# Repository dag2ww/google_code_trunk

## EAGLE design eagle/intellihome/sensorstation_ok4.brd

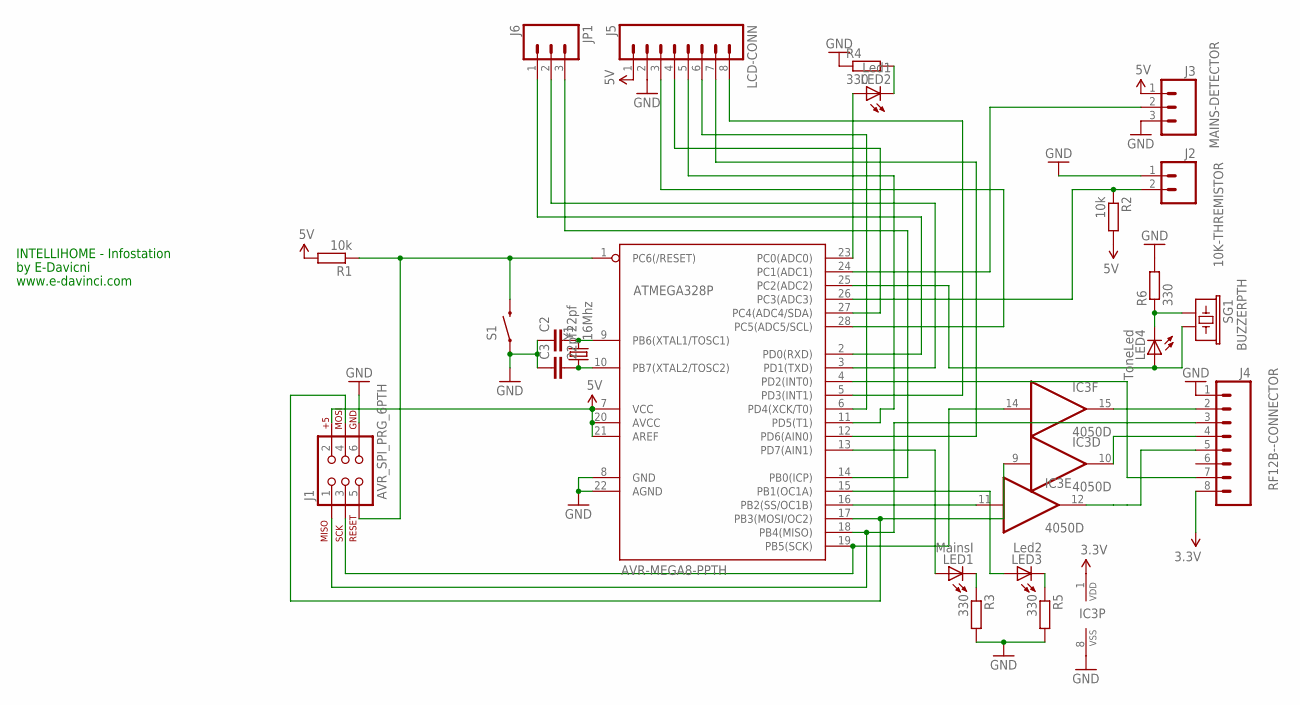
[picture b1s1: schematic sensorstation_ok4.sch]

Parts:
10K-THREMISTOR: J2; 1X02
ATMEGA328P: AVR-MEGA8-PPTH; DIL28-3
C2, C3: 22pf; CAP-PTH-SMALL
IC3: 4050D; SO16
J1: AVR_SPI_PRG_6PTH; 2X3
JP1: J6; 1X03
LCD-CONN: J5; 1X08
LED1: MainsI; LED3MM
LED2: Led1; LED3MM
LED3: Led2; LED3MM
LED4: ToneLed; LED3MM
MAINS-DETECTOR: J3; 1X03
R1, R2: 10k; 0207/2V
R3, R4, R5, R6: 330; 0207/2V
RF12B--CONNECTOR: J4; 1X08_LONGPADS
S1: SWITCH-MOMENTARY-2PTH; TACTILE-PTH
SG1: BUZZERPTH; BUZZER-12MM
Y1: 16Mhz; HC49US

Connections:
3.3V: IC3.1 (VDD), RF12B--CONNECTOR.8
5V: ATMEGA328P.7 (VCC), ATMEGA328P.20 (AVCC), ATMEGA328P.21 (AREF), J1.2, LCD-CONN.1, MAINS-DETECTOR.1, R1.2, R2.2
GND: 10K-THREMISTOR.1, ATMEGA328P.8 (GND), ATMEGA328P.22 (AGND), C2.1, C3.1, IC3.8 (VSS), J1.6, LCD-CONN.2, MAINS-DETECTOR.3, R3.2, R4.1, R5.2, R6.2, RF12B--CONNECTOR.1, S1.1
unnamed: ATMEGA328P.4 (PD2(INT0)), RF12B--CONNECTOR.7
unnamed: ATMEGA328P.16 (PB2(SS/OC1B)), IC3.11 (I)
unnamed: ATMEGA328P.19 (PB5(SCK)), IC3.14 (I), J1.3
unnamed: ATMEGA328P.17 (PB3(MOSI/OC2)), IC3.9 (I), J1.4
unnamed: IC3.10 (O), RF12B--CONNECTOR.4
unnamed: ATMEGA328P.9 (PB6(XTAL1/TOSC1)), C2.2, Y1.2
unnamed: ATMEGA328P.10 (PB7(XTAL2/TOSC2)), C3.2, Y1.1
unnamed: ATMEGA328P.24 (PC1(ADC1)), MAINS-DETECTOR.2
unnamed: 10K-THREMISTOR.2, ATMEGA328P.26 (PC3(ADC3)), R2.1
unnamed: LED1.K (C), R3.1
unnamed: LED4.K (C), R6.1, SG1.+ (1)
unnamed: LED2.K (C), R4.2
unnamed: LED3.K (C), R5.1
unnamed: ATMEGA328P.23 (PC0(ADC0)), LED2.A
unnamed: ATMEGA328P.15 (PB1(OC1A)), LED3.A
unnamed: ATMEGA328P.25 (PC2(ADC2)), LED4.A, SG1.- (2)
unnamed: ATMEGA328P.14 (PB0(ICP)), JP1.3
unnamed: IC3.15 (O), RF12B--CONNECTOR.2
unnamed: IC3.12 (O), RF12B--CONNECTOR.5
unnamed: ATMEGA328P.13 (PD7(AIN1)), LED1.A
unnamed: ATMEGA328P.18 (PB4(MISO)), J1.1, RF12B--CONNECTOR.3
unnamed: ATMEGA328P.12 (PD6(AIN0)), LCD-CONN.7
unnamed: ATMEGA328P.11 (PD5(T1)), LCD-CONN.5
unnamed: ATMEGA328P.6 (PD4(XCK/T0)), LCD-CONN.6
unnamed: ATMEGA328P.5 (PD3(INT1)), LCD-CONN.8
unnamed: ATMEGA328P.3 (PD1(TXD)), JP1.2
unnamed: ATMEGA328P.2 (PD0(RXD)), JP1.1
unnamed: ATMEGA328P.27 (PC4(ADC4/SDA)), LCD-CONN.4
unnamed: ATMEGA328P.28 (PC5(ADC5/SCL)), LCD-CONN.3
unnamed: ATMEGA328P.1 (PC6(/RESET)), J1.5, R1.1, S1.3 (2)

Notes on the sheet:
www.e-davinci.com
INTELLIHOME - Infostation
by E-Davicni

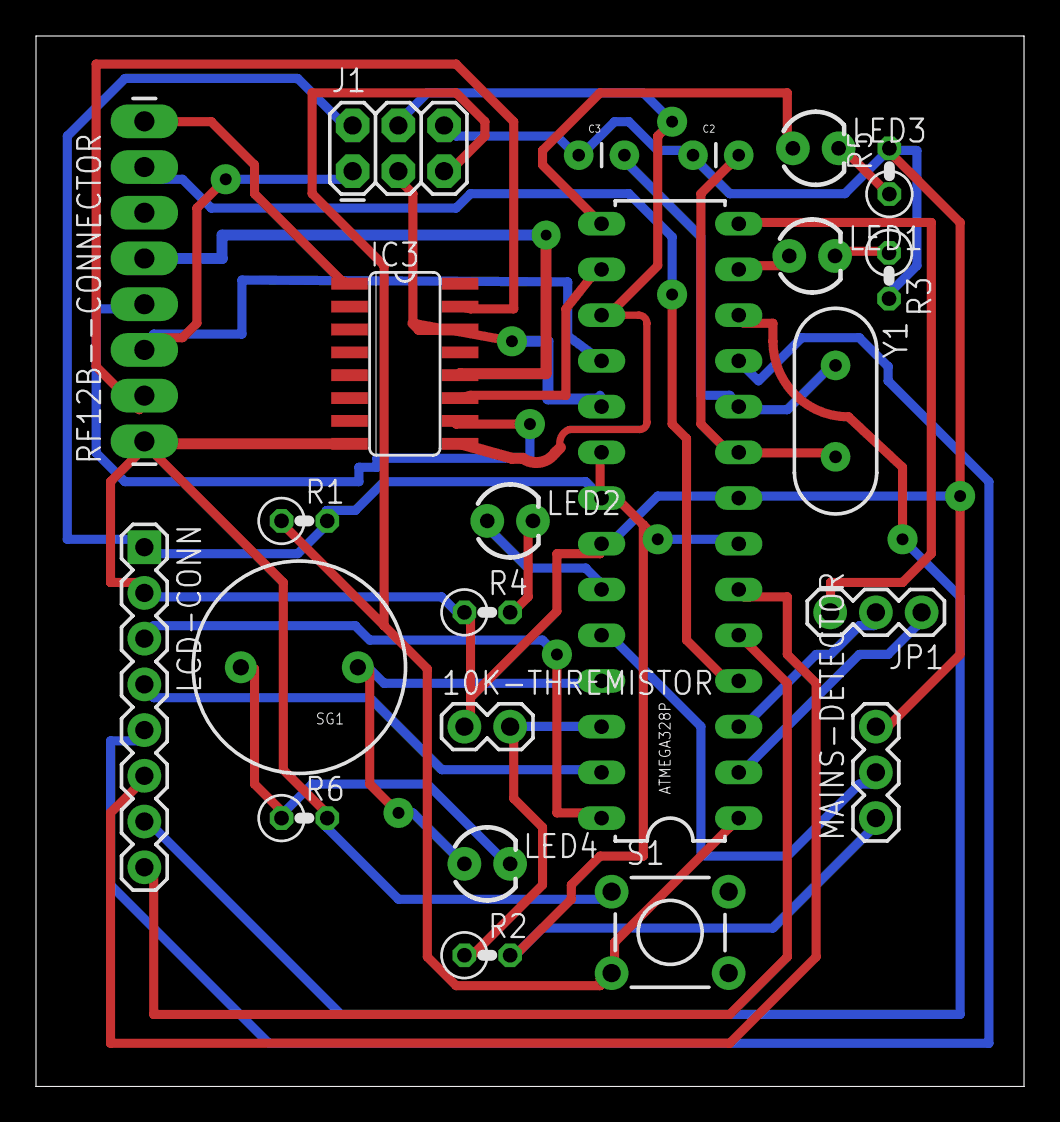
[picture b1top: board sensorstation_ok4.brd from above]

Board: 2 copper layers, 54.9 x 58.4 mm, 23 parts (0 on the bottom side), 33 nets.

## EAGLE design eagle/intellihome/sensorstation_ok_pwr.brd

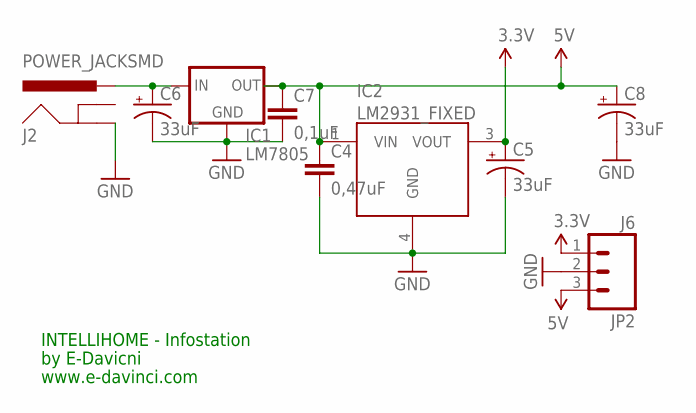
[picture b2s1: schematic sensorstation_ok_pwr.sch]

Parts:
C4: 0,47uF; CAP-PTH-SMALL-KIT
C5, C6, C8: 33uF; CPOL-RADIAL-10UF-25V
C7: 0,1uF; CAP-PTH-SMALL-KIT
IC1: LM7805; TO-220-ALT
IC2: LM2931_FIXED; DPAK
J2: POWER_JACKSMD; POWER_JACK_SMD
JP2: J6; 1X03

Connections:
3.3V: C5.1 (+), IC2.3 (VOUT), JP2.1
5V: C4.1, C7.1, C8.1 (+), IC1.OUT, IC2.1 (VIN), JP2.3
GND: C4.2, C5.2 (-), C6.2 (-), C7.2, C8.2 (-), IC1.GND, IC2.4 (GND), J2.P$4 (GND), JP2.2
unnamed: C6.1 (+), IC1.IN, J2.VIN0 (PWR)

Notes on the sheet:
www.e-davinci.com
INTELLIHOME - Infostation
by E-Davicni

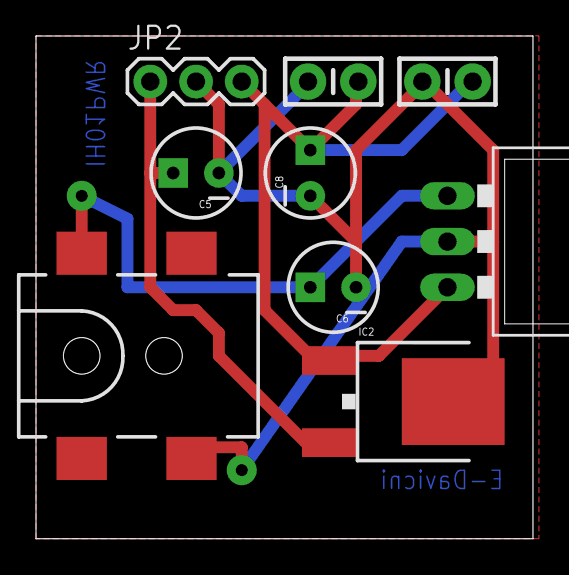
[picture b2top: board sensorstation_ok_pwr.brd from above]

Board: 2 copper layers, 27.6 x 27.9 mm, 9 parts (0 on the bottom side), 4 nets.

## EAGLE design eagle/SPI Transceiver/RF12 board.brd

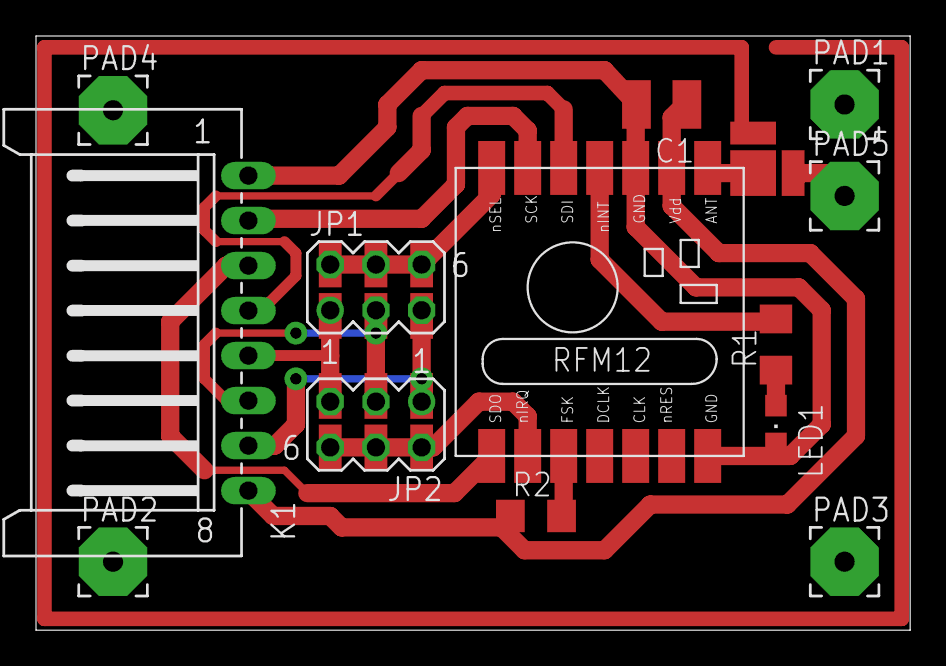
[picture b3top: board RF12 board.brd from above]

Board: 2 copper layers, 48.6 x 33.0 mm, 13 parts (0 on the bottom side), 13 nets.

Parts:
C1: C1210
JP1, JP2: MA03-2
K1: L08P
LED1: CHIPLED_0805
PAD1, PAD2, PAD3, PAD4, PAD5: 3,81/1,1
R1: 390; R1206
R2: 10K; R1206
U1: RFM12_SMDSMD; RFM12

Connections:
CS0: JP1.1, JP2.5, K1.5
CS1: JP1.3, JP2.3, K1.6
CS2: JP1.5, JP2.1, K1.7
GND: C1.2, K1.1, LED1.C, U1.7, U1.10
unnamed: K1.2, U1.13
unnamed: R1.2, U1.11
unnamed: K1.3, U1.1
unnamed: K1.4, U1.12
unnamed: R2.2, U1.3
unnamed: JP2.2, JP2.4, JP2.6, U1.2
unnamed: JP1.2, JP1.4, JP1.6, U1.14
unnamed: LED1.A, R1.1
VCC: C1.1, K1.8, R2.1, U1.9

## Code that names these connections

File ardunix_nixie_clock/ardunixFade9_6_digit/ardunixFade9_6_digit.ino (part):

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
// SN74141/K155ID1
// These are now managed directly on PORT B, we don't use digitalWrite() for these
#define ledPin_0_a  13    // package pin 19 // PB5
#define ledPin_0_b  10    // package pin 16 // PB2
#define ledPin_0_c  8     // package pin 14 // PB0
#define ledPin_0_d  12    // package pin 18 // PB4

// anode pins
#define ledPin_a_6  0     // low  - Secs  units // package pin 2  // PD0
#define ledPin_a_5  1     //      - Secs  tens  // package pin 3  // PD1
#define ledPin_a_4  2     //      - Mins  units // package pin 4  // PD2
#define ledPin_a_3  4     //      - Mins  tens  // package pin 6  // PD4
#define ledPin_a_2  A2    //      - Hours units // package pin 25 // PC2
#define ledPin_a_1  A3    // high - Hours tens  // package pin 26 // PC3

// button input
#define inputPin1   7     // package pin 13 // PD7

// PWM pin used to drive the DC-DC converter
#define hvDriverPin 9     // package pin 15 // PB1

// Tick led - PWM capable
#define tickLed     11    // package pin 17 // PB3

// PWM capable output for backlight
#define RLed        6     // package pin 12 // PD6
#define GLed        5     // package pin 11 // PD5
#define BLed        3     // package pin 5  // PD3

#define sensorPin   A0    // Package pin 23 // PC0 // Analog input pin for HV sense: HV divided through 390k and 4k7 divider, using 5V reference
#define LDRPin      A1    // Package pin 24 // PC1 // Analog input for Light dependent resistor.

//**********************************************************************************

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
  tccrOff = TCCR1A;

  TCCR1A |= (1 <<  COM1A1);  // enable PWM on port PD4 in non-inverted compare mode 2

  tccrOn = TCCR1A;

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// ************************************************************
void digitOn(int digit, int value) {
  switch (digit) {
    case 0: PORTC = PORTC | B00001000; break; // PC3 - equivalent to digitalWrite(ledPin_a_1,HIGH);
    case 1: PORTC = PORTC | B00000100; break; // PC2 - equivalent to digitalWrite(ledPin_a_2,HIGH);
    case 2: PORTD = PORTD | B00010000; break; // PD4 - equivalent to digitalWrite(ledPin_a_3,HIGH);
    case 3: PORTD = PORTD | B00000100; break; // PD2 - equivalent to digitalWrite(ledPin_a_4,HIGH);
    case 4: PORTD = PORTD | B00000010; break; // PD1 - equivalent to digitalWrite(ledPin_a_5,HIGH);
    case 5: PORTD = PORTD | B00000001; break; // PD0 - equivalent to digitalWrite(ledPin_a_6,HIGH);
  }
  SetSN74141Chip(value);
  TCCR1A = tccrOn;
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
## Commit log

2017-09-11 :circus_tent: Added .gitattributes & .gitignore files
2017-09-11 initial commit
    all stuff
2017-09-11 added prints
2017-09-14 Full working version with possible to chenge secret
2017-09-20 next
2017-09-24 Another Frequency generator with duty
2017-09-25 adjusted frequencies
2017-11-05 added freq gen ok
2017-11-26 Added main projects
2017-11-27 Added ESP BLYNK projects
2017-12-05 esp weather station adn libs
2017-12-10 first vers all works
2018-02-04 Removed wrong weather station project
    and added forecast for all sensors
2018-03-08 fixed cimpilation of blynk
2019-06-20 Create distance_guard_sound_trigger.ino
    added light trigger based on distance
2019-08-21 sim800l service handling added
    sim800l service handling added
2020-04-23 added nixie tube
2020-05-13 Update nixie_tube.ino
    add RTC reading
2020-06-04 added real nixie clock stuff ardunix
2020-06-04 ardunix
2020-06-07 add nixie tube clock
2020-06-10 added joyc and roverc
2020-06-25 add final and working version of nixie
2020-10-16 add 8bit games sim
2021-01-03 Create bugc_szymek_autko01.m5f
    buc receiver based realy controller for szymek auto control
2021-01-24 added keyboard joy
2021-02-25 it works i2c
2021-02-25 it works i2c and buttons
2021-02-25 workspace2 code same
2021-03-10 next iter working

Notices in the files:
parts and their libraries:
SparkFun: Licensing: CC v3.0 Share-Alike You are welcome to use this library for commercial purposes.
